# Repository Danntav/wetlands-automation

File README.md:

# Wetlands Automation System

An IoT-based automation system for monitoring and controlling wetland reactors in environmental research applications.

## Overview

This system implements a complete automation solution for wetland reactor monitoring using a distributed sensor network. The architecture consists of a master ESP32 unit with embedded HMI (LCD display and joystick) that coordinates data collection from up to 9 slave units via ESP-NOW wireless protocol. The master unit manages local control, real-time visualization, alarm monitoring, and fault-tolerant data logging to SD card.

## System Architecture

The system uses a master-slave architecture where the master ESP32 coordinates periodic data collection from distributed slave units. Communication is handled via ESP-NOW protocol for low-power wireless operation. The master unit features an interactive HMI for field operation, stores timestamped data with fault redundancy using an RTC module, and implements comprehensive alarm management for sensor anomalies and communication timeouts.

## Hardware Components

**Master Unit:**
- ESP32 microcontroller
- ST7735 LCD display (SPI interface)
- Analog joystick for menu navigation
- DS1307 RTC module (I2C)
- SD card module for data logging
- 3x RGB LED indicators for system status
- Custom PCB designed in KiCAD
- 3D-printed enclosure (SolidWorks)

**Slave Units:**
- ESP32 microcontroller
- Voltage and temperature sensors
- Wireless communication via ESP-NOW

## Software Implementation

The firmware is written in C/C++ using the Arduino framework. Key features include:

- **ESP-NOW Communication:** Implements request-response protocol with ACK for reliable data transfer between master and slaves
- **Real-time Clock:** DS1307 RTC provides accurate timestamps for all data points
- **Data Collection Cycle:** Configurable 30-minute intervals for automated sensor polling
- **Buffered Writing:** Collects data from all slaves before writing to SD card to minimize file operations
- **Alarm System:** Monitors voltage thresholds, temperature ranges, sensor failures, and communication timeouts
- **Interactive HMI:** Multi-screen menu system for viewing live data, historical logs, system status, and alarms
- **Fault Tolerance:** Redundant write verification and error recovery mechanisms

### Libraries Used

- **ESP-NOW & WiFi** version & version 1.2.7, Wireless communication stack
- **RTClib** version 2.1.4, DS1307 real-time clock interface
- **SD** version 1.3.0, SD card file system management
- **Adafruit_GFX & Adafruit_ST7735** version 1.12.1 & version 1.11.0, Display graphics and ST7735 driver
- **Wire** I2C communication for RTC

## Key Features

- Automatic data collection at configurable intervals (default: 30 minutes)
- Support for up to 9 distributed slave nodes
- Real-time monitoring with timestamped data
- Comprehensive alarm system with visual and logged notifications
- Field-accessible HMI with joystick navigation
- CSV data format for easy post-processing
- System health monitoring with LED status indicators
- Communication timeout detection and alerts

## Getting Started

### Hardware Setup

1. Assemble the master PCB with ESP32, display, RTC, SD module, and joystick
2. Install components in the 3D-printed enclosure
3. Program each slave unit with unique MAC address
4. Deploy slave units at monitoring locations
5. Power on the system and verify all slaves are detected

### Software Installation

```bash
git clone https://github.com/Danntav/wetlands-automation.git
cd wetlands-automation
```

Install required libraries in Arduino IDE, configure ESP32 board settings, and update slave MAC addresses in the master firmware before uploading.

## Project Structure

```
wetlands-automation/
├── firmware/
│   ├── master/
│   │   ├── master.ino
│   │   ├── MenuManager.h
│   │   ├── LedAnimations.h
│   │   └── DataStructures.h
│   └── slave/
├── hardware/
│   ├── pcb/              # KiCAD PCB files
│   └── enclosure/        # SolidWorks 3D models
└── docs/
```

## HMI Operation

The embedded Human-Machine Interface provides:
- **Main Menu:** System overview with active slave count and last update times
- **Board Data:** Individual slave readings with voltage and temperature
- **Alarms:** Real-time alerts for sensor anomalies and communication failures
- **Error Log:** Historical system errors with timestamps
- **System Info:** RTC status, SD card status, and overall health

Navigation is performed using the analog joystick (up/down/left/right/click).

## Data Logging

Data is logged in CSV format with the following structure:
```
Date,Time,BoardID,Voltage,Temperature
```

The system implements:
- Buffered writes to minimize SD card wear
- Automatic file creation with headers
- Timestamp verification via RTC
- Error logging for failed operations
- Visual feedback via LED indicators

## Alarm System

The system monitors and alerts for:
- Voltage readings outside safe range (configurable thresholds)
- Temperature anomalies beyond expected limits
- Sensor hardware failures (invalid readings)
- Communication timeouts (no response from slaves)

Alarms are displayed on the HMI, stored in memory, and indicated via blinking red LED.

## Configuration

System parameters can be adjusted in the firmware:
- `COLLECTION_INTERVAL_MS`: Data collection frequency (default: 30 minutes)
- `VOLTAGE_MIN/MAX`: Voltage alarm thresholds
- `TEMP_MIN/MAX`: Temperature alarm thresholds
- `COMM_TIMEOUT_MS`: Communication timeout duration
- `TOTAL_SLAVES`: Number of connected slave units

## Contributing

Contributions, issues, and feature requests are welcome. Feel free to check the issues page or submit pull requests.

## License

MIT License - see [LICENSE](LICENSE) file for details.

## Author

**Daniel Oliveira Tavares**

LinkedIn: [daniel-otavares](https://www.linkedin.com/in/daniel-otavares)

Email: danieloftavares@gmail.com

GitHub: [@Danntav](https://github.com/Danntav)

## Future Improvements

- [ ] Cloud connectivity for remote monitoring via MQTT or HTTP
- [ ] Mobile app integration for real-time alerts
- [ ] Additional sensor types (pH, dissolved oxygen, flow rate)
- [ ] Solar power system with battery management
- [ ] Web dashboard for data visualization and historical analysis
- [ ] Machine learning for predictive maintenance
- [ ] LoRa support for extended range communication

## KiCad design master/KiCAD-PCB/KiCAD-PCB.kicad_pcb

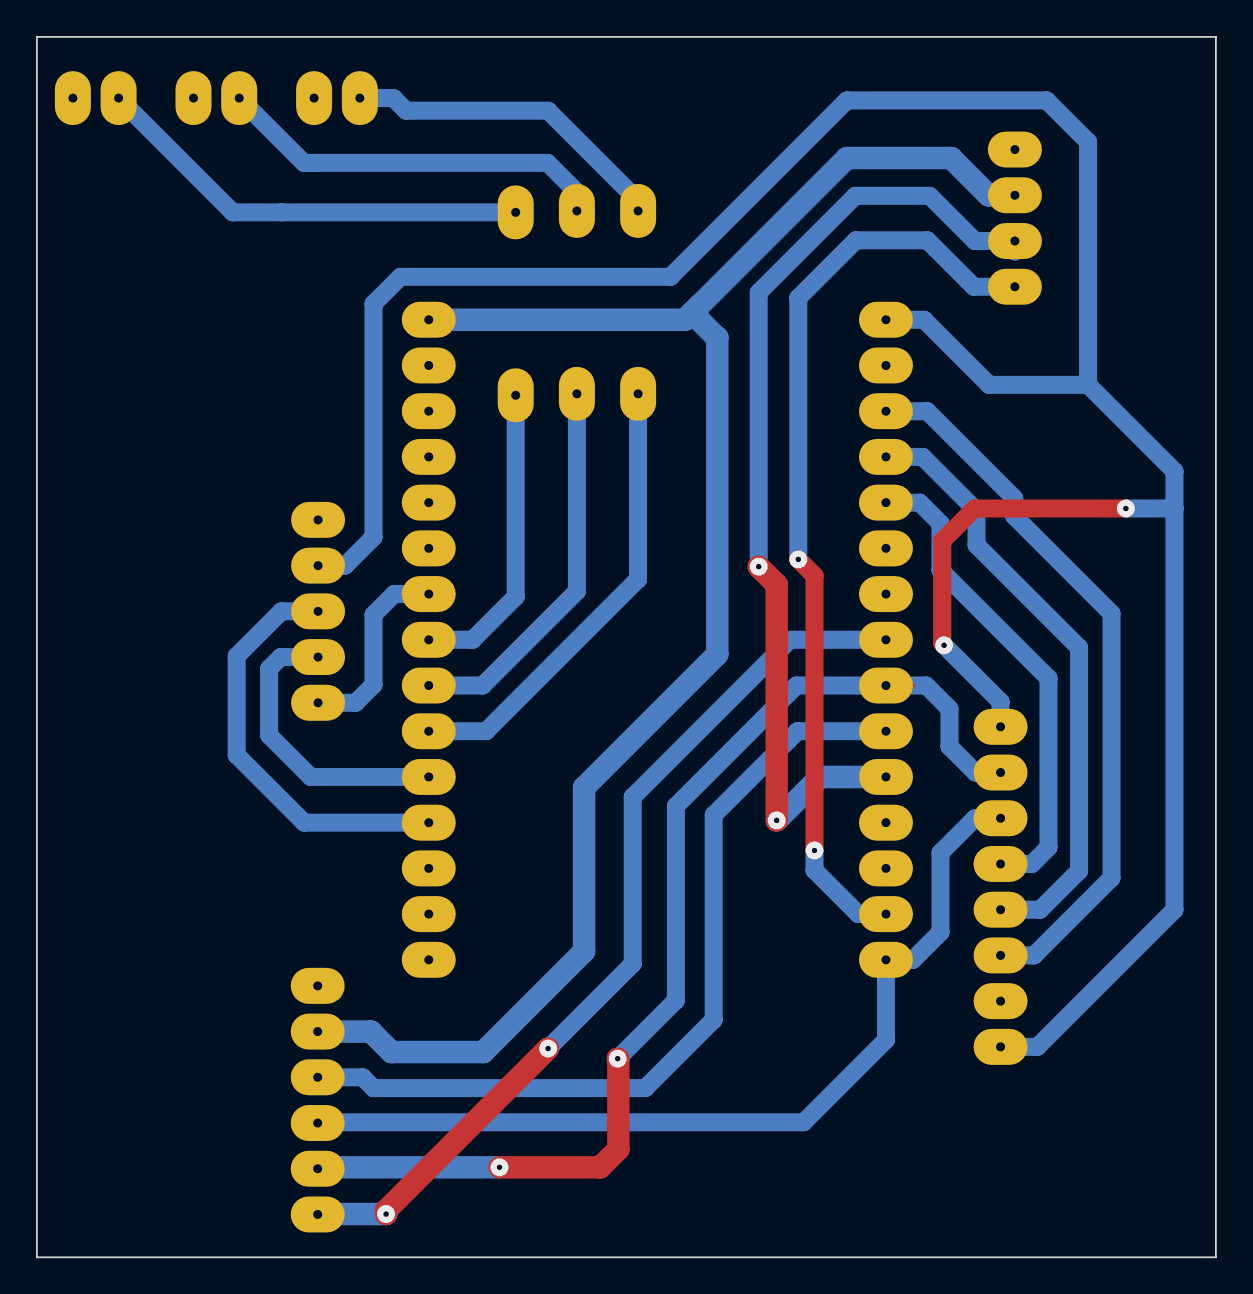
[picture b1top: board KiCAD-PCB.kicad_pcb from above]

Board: 2 copper layers, 65.5 x 67.8 mm, 11 parts (1 on the bottom side), 21 nets.

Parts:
ESP32: MODULE_ESP32_DEVKIT_V1
J1: Conn_01x08_Pin; PinSocket_1x08_P2.54mm_Vertical
Joystick1: PinSocket_1x05_P2.54mm_Vertical
LED1: LED1; LED_D5.0mm
LED2: LED2; LED_D5.0mm
LED3: LED3; LED_D5.0mm
MicroSD: Micro_SD_Card; PinSocket_1x06_P2.54mm_Vertical
R1, R2, R3: 220Ohm; R_Axial_DIN0207_L6.3mm_D2.5mm_P10.16mm_Horizontal
RTC: Conn_01x04_Pin; PinSocket_1x04_P2.54mm_Vertical

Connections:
+3.3V: ESP32.16 (3.3v), J1.1, J1.8, Joystick1.4 (VRY)
+5V: ESP32.1 (VIN), MicroSD.5 (VCC), RTC.3
GND: ESP32.2 (GND), ESP32.17 (GND), J1.7, Joystick1.5 (SW), LED1.1 (K), LED2.1 (K), LED3.1 (K), MicroSD.6 (GND), RTC.4
GPIO02: ESP32.19 (GPIO2), J1.5
GPIO04: ESP32.20 (GPIO4), J1.4
GPIO05: ESP32.23 (GPIO5), MicroSD.1 (CS)
GPIO15: ESP32.18 (GPIO15), J1.6
GPIO18: ESP32.24 (GPIO18), J1.2, MicroSD.2 (SCK)
GPIO19: ESP32.25 (GPIO19), MicroSD.4 (MISO)
GPIO21: ESP32.26 (GPIO21), RTC.2
GPIO22: ESP32.29 (GPIO22), RTC.1
GPIO23: ESP32.30 (GPIO23), J1.3, MicroSD.3 (MOSI)
GPIO25: ESP32.8 (GPIO25), R3.2
GPIO26: ESP32.7 (GPIO26), Joystick1.1 (GND)
GPIO32: ESP32.10 (GPIO32), R1.2
GPIO33: ESP32.9 (GPIO33), R2.2
GPIO34: ESP32.12 (GPIO34), Joystick1.3 (VRX)
GPIO35: ESP32.11 (GPIO35), Joystick1.2 (+5V)
unnamed: LED1.2 (A), R1.1
unnamed: LED2.2 (A), R2.1
unnamed: LED3.2 (A), R3.1

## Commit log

2025-07-13 ack, button wakeup, US added
2025-07-14 Split sensor functions; LED functions; Average sensors measurements
2025-07-15 led animation added; average US; bug ackrev resolved
2025-07-16 master reworked; ACK; SD card logic; led libs
2025-07-17 display&joystick logic with menu; data struct splitted; get Mac ESP32 example; bug ESP32 stuck on led loops; setup functions
2025-07-18 sender->slave; resolved bug flicker display; animation display; getMAC improved; scanI2C example for RTC; KiCAD project created
2025-07-19 Moved test to specif folder; master setup reorganized; register slave; setupSD reworked + added handleJoystick func; errorMsgACK; scanI2C;
2025-07-19 set all definitions into DataStructs.h
2025-07-19 removed duplicated .h/.cpp files
2025-07-29 bug SPI modules conflict resolved
2025-08-06 config real ESPs' MAC
2025-09-19 3D Files, PCB board, code update
2025-09-24 Incresed container volume; Updated screen menu
2025-09-26 Menu reworked; ESP-NOW updated
2025-09-26 Bug menu fixed; ACK message reworked
2025-09-26 SPI bug fixed; ACK bug fixed
2025-09-27 Slave9 MAC; Better menu view; ACK duplicate
2025-09-29 increased voltage range; better mV visualization; bug timeout fixed
2025-09-30 Timestamp in .csv subdivided; min temp fixed
2025-09-30 Removing not using func/var
2025-09-30 removed excessive comments
2025-10-27 Collect data timer increased
2025-10-27 Added README file
